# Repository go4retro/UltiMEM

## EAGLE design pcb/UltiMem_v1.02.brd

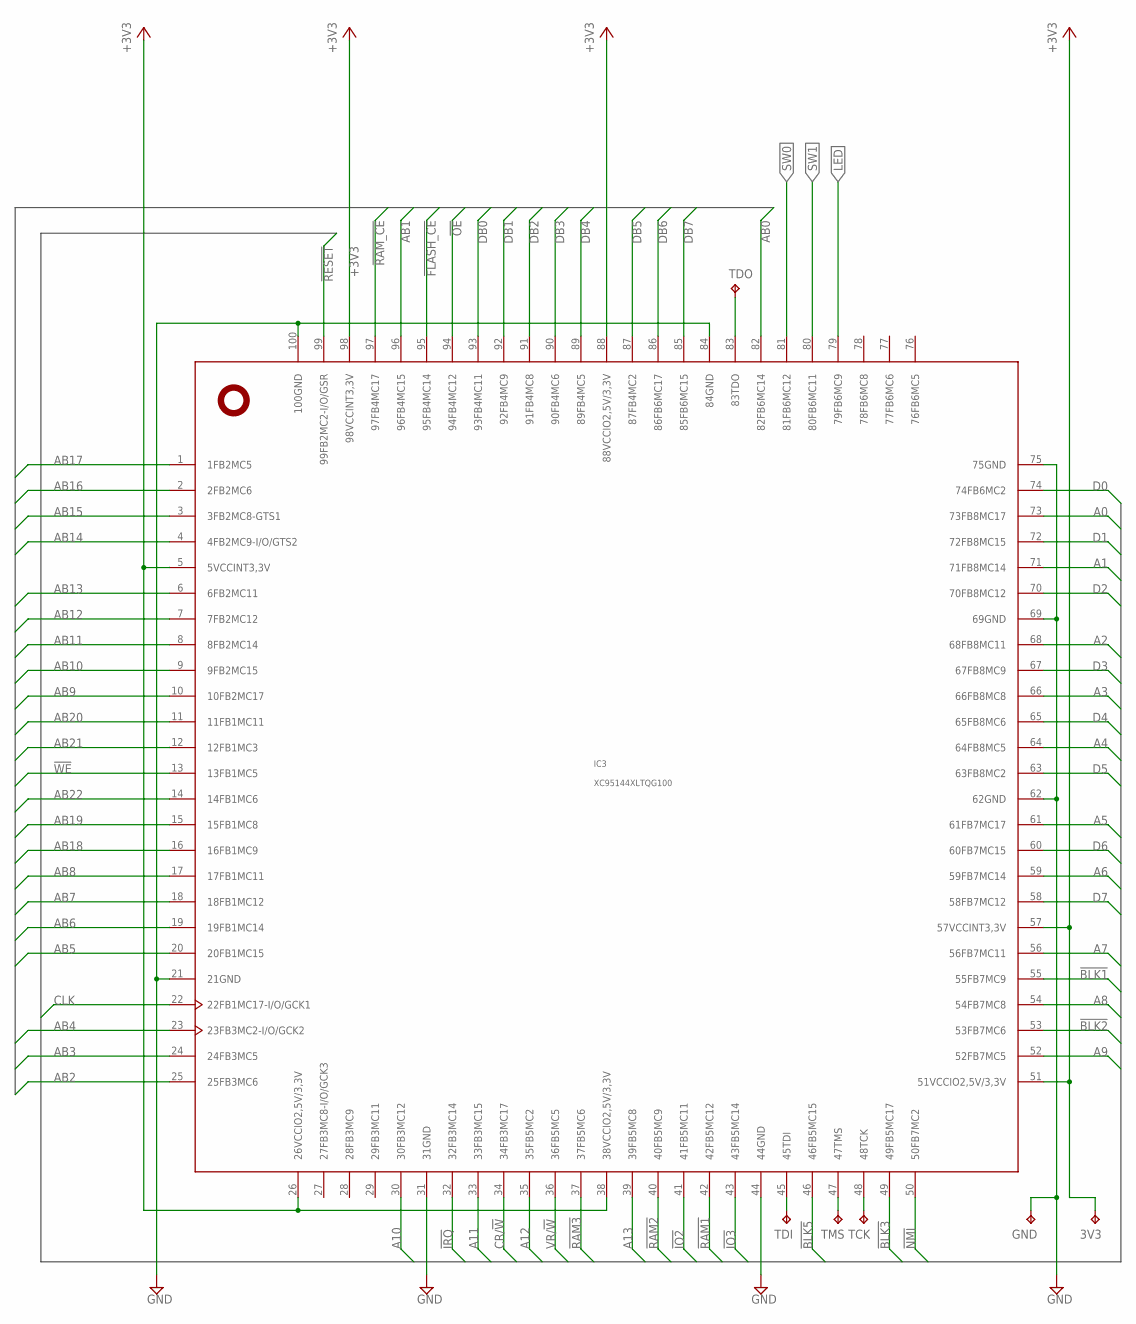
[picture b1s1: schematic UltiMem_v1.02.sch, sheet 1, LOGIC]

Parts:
3V3: TPTP08R; TP08R
GND: TPTP08R; TP08R
IC3: XC95144XLTQG100; TQFP100
TCK: TPTP08R; TP08R
TDI: TPTP08R; TP08R
TDO: TPTP08R; TP08R
TMS: TPTP08R; TP08R

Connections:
!BLK1: IC3.55 (55FB7MC9); also elsewhere on the board
!BLK2: IC3.53 (53FB7MC6); also elsewhere on the board
!BLK3: IC3.49 (49FB5MC17); also elsewhere on the board
!BLK5: IC3.46 (46FB5MC15); also elsewhere on the board
!FLASH_CE: IC3.95 (95FB4MC14); also elsewhere on the board
!IO2: IC3.41 (41FB5MC11); also elsewhere on the board
!IO3: IC3.43 (43FB5MC14); also elsewhere on the board
!IRQ: IC3.32 (32FB3MC14); also elsewhere on the board
!NMI: IC3.50 (50FB7MC2); also elsewhere on the board
!OE: IC3.94 (94FB4MC12); also elsewhere on the board
!RAM1: IC3.42 (42FB5MC12); also elsewhere on the board
!RAM2: IC3.40 (40FB5MC9); also elsewhere on the board
!RAM3: IC3.37 (37FB5MC6); also elsewhere on the board
!RAM_CE: IC3.97 (97FB4MC17); also elsewhere on the board
!RESET: IC3.99 (99FB2MC2-I/O/GSR); also elsewhere on the board
!WE: IC3.13 (13FB1MC5); also elsewhere on the board
+3V3: 3V3.TP, IC3.5 (5VCCINT3,3V), IC3.26 (26VCCIO2,5V/3,3V), IC3.38 (38VCCIO2,5V/3,3V), IC3.51 (51VCCIO2,5V/3,3V), IC3.57 (57VCCINT3,3V), IC3.88 (88VCCIO2,5V/3,3V), IC3.98 (98VCCINT3,3V); also elsewhere on the board
A0: IC3.73 (73FB8MC17); also elsewhere on the board
A1: IC3.71 (71FB8MC14); also elsewhere on the board
A2: IC3.68 (68FB8MC11); also elsewhere on the board
A3: IC3.66 (66FB8MC8); also elsewhere on the board
A4: IC3.64 (64FB8MC5); also elsewhere on the board
A5: IC3.61 (61FB7MC17); also elsewhere on the board
A6: IC3.59 (59FB7MC14); also elsewhere on the board
A7: IC3.56 (56FB7MC11); also elsewhere on the board
A8: IC3.54 (54FB7MC8); also elsewhere on the board
A9: IC3.52 (52FB7MC5); also elsewhere on the board
A10: IC3.30 (30FB3MC12); also elsewhere on the board
A11: IC3.33 (33FB3MC15); also elsewhere on the board
A12: IC3.35 (35FB5MC2); also elsewhere on the board
A13: IC3.39 (39FB5MC8); also elsewhere on the board
AB0: IC3.82 (82FB6MC14); also elsewhere on the board
AB1: IC3.96 (96FB4MC15); also elsewhere on the board
AB2: IC3.25 (25FB3MC6); also elsewhere on the board
AB3: IC3.24 (24FB3MC5); also elsewhere on the board
AB4: IC3.23 (23FB3MC2-I/O/GCK2); also elsewhere on the board
AB5: IC3.20 (20FB1MC15); also elsewhere on the board
AB6: IC3.19 (19FB1MC14); also elsewhere on the board
AB7: IC3.18 (18FB1MC12); also elsewhere on the board
AB8: IC3.17 (17FB1MC11); also elsewhere on the board
AB9: IC3.10 (10FB2MC17); also elsewhere on the board
AB10: IC3.9 (9FB2MC15); also elsewhere on the board
AB11: IC3.8 (8FB2MC14); also elsewhere on the board
AB12: IC3.7 (7FB2MC12); also elsewhere on the board
AB13: IC3.6 (6FB2MC11); also elsewhere on the board
AB14: IC3.4 (4FB2MC9-I/O/GTS2); also elsewhere on the board
AB15: IC3.3 (3FB2MC8-GTS1); also elsewhere on the board
AB16: IC3.2 (2FB2MC6); also elsewhere on the board
AB17: IC3.1 (1FB2MC5); also elsewhere on the board
AB18: IC3.16 (16FB1MC9); also elsewhere on the board
AB19: IC3.15 (15FB1MC8); also elsewhere on the board
AB20: IC3.11 (11FB1MC11); also elsewhere on the board
AB21: IC3.12 (12FB1MC3); also elsewhere on the board
AB22: IC3.14 (14FB1MC6); also elsewhere on the board
CLK: IC3.22 (22FB1MC17-I/O/GCK1); also elsewhere on the board
CR/!W: IC3.34 (34FB3MC17); also elsewhere on the board
D0: IC3.74 (74FB6MC2); also elsewhere on the board
D1: IC3.72 (72FB8MC15); also elsewhere on the board
D2: IC3.70 (70FB8MC12); also elsewhere on the board
D3: IC3.67 (67FB8MC9); also elsewhere on the board
D4: IC3.65 (65FB8MC6); also elsewhere on the board
D5: IC3.63 (63FB8MC2); also elsewhere on the board
D6: IC3.60 (60FB7MC15); also elsewhere on the board
D7: IC3.58 (58FB7MC12); also elsewhere on the board
DB0: IC3.93 (93FB4MC11); also elsewhere on the board
DB1: IC3.92 (92FB4MC9); also elsewhere on the board
DB2: IC3.91 (91FB4MC8); also elsewhere on the board
DB3: IC3.90 (90FB4MC6); also elsewhere on the board
DB4: IC3.89 (89FB4MC5); also elsewhere on the board
DB5: IC3.87 (87FB4MC2); also elsewhere on the board
DB6: IC3.86 (86FB6MC17); also elsewhere on the board
DB7: IC3.85 (85FB6MC15); also elsewhere on the board
GND: GND.TP, IC3.21 (21GND), IC3.31 (31GND), IC3.44 (44GND), IC3.62 (62GND), IC3.69 (69GND), IC3.75 (75GND), IC3.84 (84GND), IC3.100 (100GND); also elsewhere on the board
LED: IC3.79 (79FB6MC9); also elsewhere on the board
unnamed: IC3.45 (45TDI), TDI.TP
unnamed: IC3.47 (47TMS), TMS.TP
unnamed: IC3.48 (48TCK), TCK.TP
unnamed: IC3.83 (83TDO), TDO.TP
SW0: IC3.81 (81FB6MC12); also elsewhere on the board
SW1: IC3.80 (80FB6MC11); also elsewhere on the board
VR/!W: IC3.36 (36FB5MC5); also elsewhere on the board

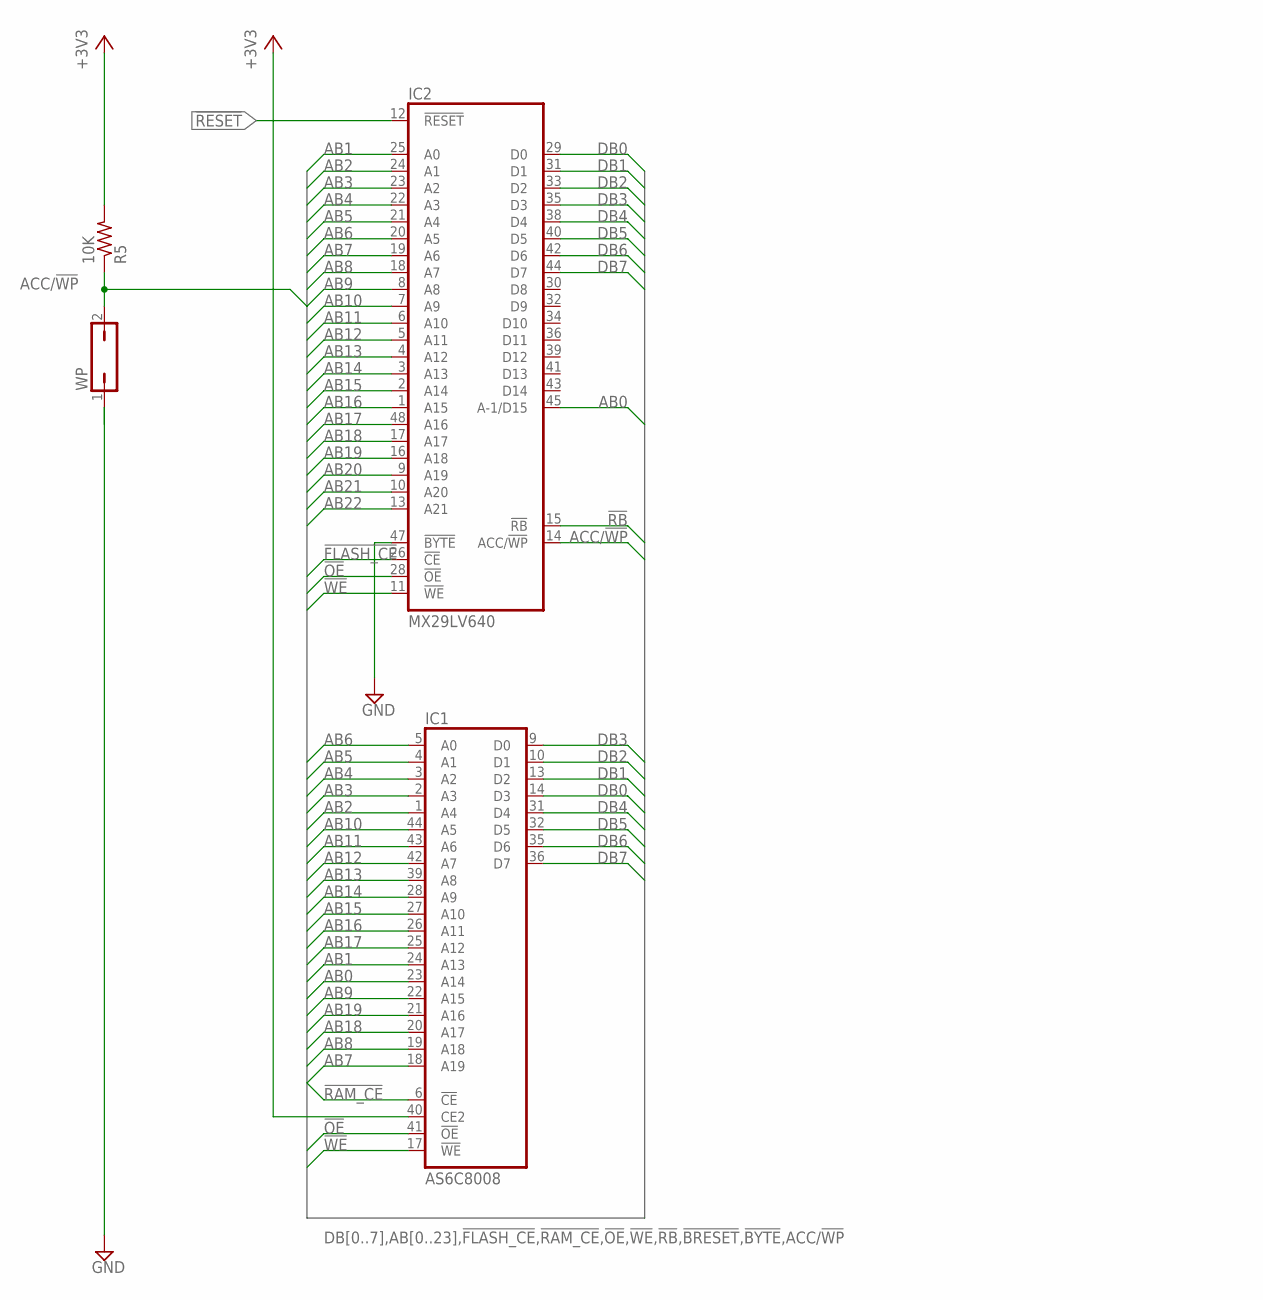
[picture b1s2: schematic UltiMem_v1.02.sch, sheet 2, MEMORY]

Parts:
IC1: AS6C8008; TSOP44
IC2: MX29LV640; TSOP48
R5: 10K; R0402
WP: JP1Q; JP1

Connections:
!FLASH_CE: IC2.26 (!CE); also elsewhere on the board
!OE: IC1.41 (!OE), IC2.28 (!OE); also elsewhere on the board
!RAM_CE: IC1.6 (!CE); also elsewhere on the board
!RB: IC2.15 (!RB)
!RESET: IC2.12 (!RESET); also elsewhere on the board
!WE: IC1.17 (!WE), IC2.11 (!WE); also elsewhere on the board
+3V3: IC1.40 (CE2), R5.2; also elsewhere on the board
AB0: IC1.23 (A14), IC2.45 (A-1/D15); also elsewhere on the board
AB1: IC1.24 (A13), IC2.25 (A0); also elsewhere on the board
AB2: IC1.1 (A4), IC2.24 (A1); also elsewhere on the board
AB3: IC1.2 (A3), IC2.23 (A2); also elsewhere on the board
AB4: IC1.3 (A2), IC2.22 (A3); also elsewhere on the board
AB5: IC1.4 (A1), IC2.21 (A4); also elsewhere on the board
AB6: IC1.5 (A0), IC2.20 (A5); also elsewhere on the board
AB7: IC1.18 (A19), IC2.19 (A6); also elsewhere on the board
AB8: IC1.19 (A18), IC2.18 (A7); also elsewhere on the board
AB9: IC1.22 (A15), IC2.8 (A8); also elsewhere on the board
AB10: IC1.44 (A5), IC2.7 (A9); also elsewhere on the board
AB11: IC1.43 (A6), IC2.6 (A10); also elsewhere on the board
AB12: IC1.42 (A7), IC2.5 (A11); also elsewhere on the board
AB13: IC1.39 (A8), IC2.4 (A12); also elsewhere on the board
AB14: IC1.28 (A9), IC2.3 (A13); also elsewhere on the board
AB15: IC1.27 (A10), IC2.2 (A14); also elsewhere on the board
AB16: IC1.26 (A11), IC2.1 (A15); also elsewhere on the board
AB17: IC1.25 (A12), IC2.48 (A16); also elsewhere on the board
AB18: IC1.20 (A17), IC2.17 (A17); also elsewhere on the board
AB19: IC1.21 (A16), IC2.16 (A18); also elsewhere on the board
AB20: IC2.9 (A19); also elsewhere on the board
AB21: IC2.10 (A20); also elsewhere on the board
AB22: IC2.13 (A21); also elsewhere on the board
ACC/!WP: IC2.14 (ACC/!WP), R5.1, WP.2
DB0: IC1.14 (D3), IC2.29 (D0); also elsewhere on the board
DB1: IC1.13 (D2), IC2.31 (D1); also elsewhere on the board
DB2: IC1.10 (D1), IC2.33 (D2); also elsewhere on the board
DB3: IC1.9 (D0), IC2.35 (D3); also elsewhere on the board
DB4: IC1.31 (D4), IC2.38 (D4); also elsewhere on the board
DB5: IC1.32 (D5), IC2.40 (D5); also elsewhere on the board
DB6: IC1.35 (D6), IC2.42 (D6); also elsewhere on the board
DB7: IC1.36 (D7), IC2.44 (D7); also elsewhere on the board
GND: IC2.47 (!BYTE), WP.1; also elsewhere on the board

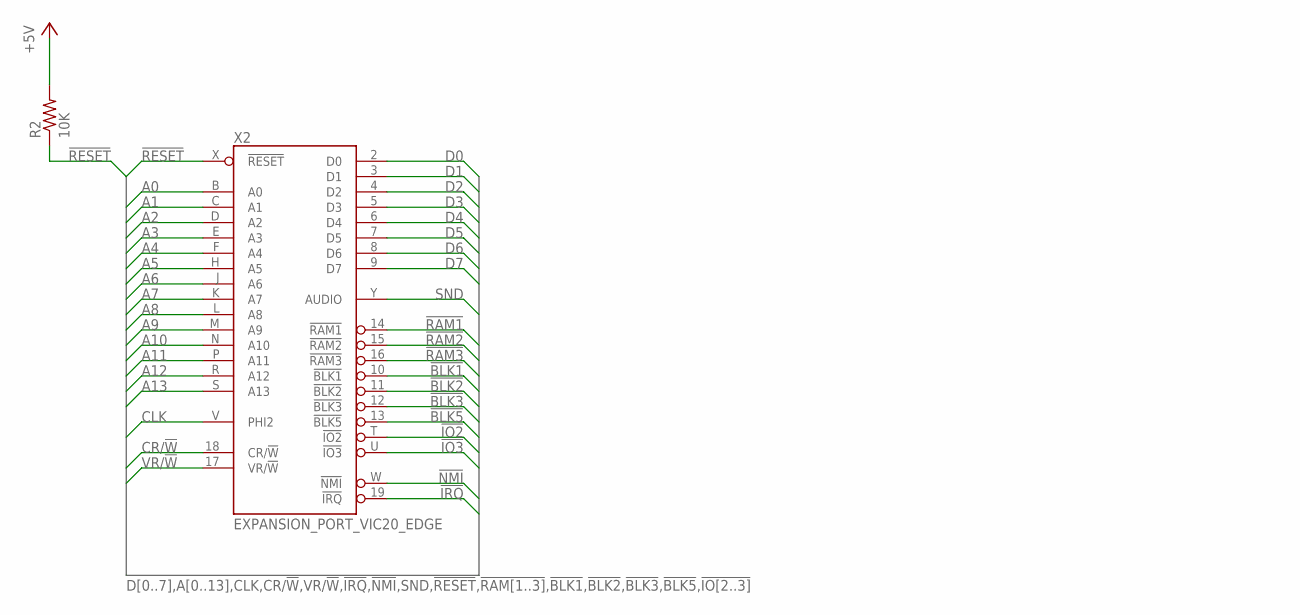
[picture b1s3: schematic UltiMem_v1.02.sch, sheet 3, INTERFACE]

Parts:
R2: 10K; R0402
X2: EXPANSION_PORT_VIC20_EDGE; MA156-22-2

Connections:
!BLK1: X2.10 (!BLK1); also elsewhere on the board
!BLK2: X2.11 (!BLK2); also elsewhere on the board
!BLK3: X2.12 (!BLK3); also elsewhere on the board
!BLK5: X2.13 (!BLK5); also elsewhere on the board
!IO2: X2.T (!IO2); also elsewhere on the board
!IO3: X2.U (!IO3); also elsewhere on the board
!IRQ: X2.19 (!IRQ); also elsewhere on the board
!NMI: X2.W (!NMI); also elsewhere on the board
!RAM1: X2.14 (!RAM1); also elsewhere on the board
!RAM2: X2.15 (!RAM2); also elsewhere on the board
!RAM3: X2.16 (!RAM3); also elsewhere on the board
!RESET: R2.1, X2.X (!RESET); also elsewhere on the board
+5V: R2.2; also elsewhere on the board
A0: X2.B (A0); also elsewhere on the board
A1: X2.C (A1); also elsewhere on the board
A2: X2.D (A2); also elsewhere on the board
A3: X2.E (A3); also elsewhere on the board
A4: X2.F (A4); also elsewhere on the board
A5: X2.H (A5); also elsewhere on the board
A6: X2.J (A6); also elsewhere on the board
A7: X2.K (A7); also elsewhere on the board
A8: X2.L (A8); also elsewhere on the board
A9: X2.M (A9); also elsewhere on the board
A10: X2.N (A10); also elsewhere on the board
A11: X2.P (A11); also elsewhere on the board
A12: X2.R (A12); also elsewhere on the board
A13: X2.S (A13); also elsewhere on the board
CLK: X2.V (PHI2); also elsewhere on the board
CR/!W: X2.18 (CR/!W); also elsewhere on the board
D0: X2.2 (D0); also elsewhere on the board
D1: X2.3 (D1); also elsewhere on the board
D2: X2.4 (D2); also elsewhere on the board
D3: X2.5 (D3); also elsewhere on the board
D4: X2.6 (D4); also elsewhere on the board
D5: X2.7 (D5); also elsewhere on the board
D6: X2.8 (D6); also elsewhere on the board
D7: X2.9 (D7); also elsewhere on the board
SND: X2.Y (AUDIO)
VR/!W: X2.17 (VR/!W); also elsewhere on the board

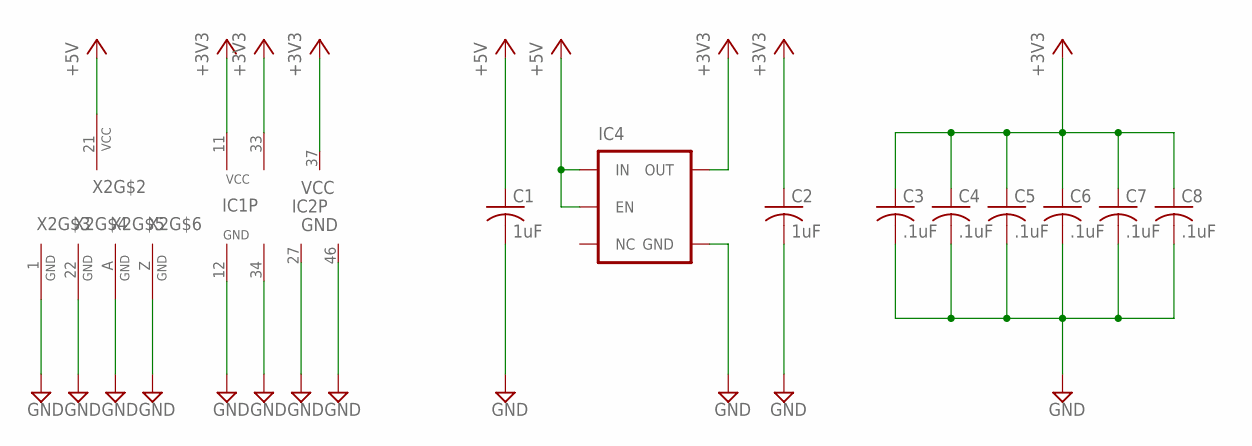
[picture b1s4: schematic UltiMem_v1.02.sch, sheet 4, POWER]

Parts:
C1, C2: 1uF; C0402
C3, C4, C5, C6, C7, C8: .1uF; C0402
IC1: AS6C8008; TSOP44
IC2: MX29LV640; TSOP48
IC4: V_REG_TPS76433SOT23-5; SOT23-5
X2: EXPANSION_PORT_VIC20_EDGE; MA156-22-2

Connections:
+3V3: C2.1, C3.1, C4.1, C5.1, C6.1, C7.1, C8.1, IC1.11 (VCC), IC1.33 (VCC), IC2.37 (VCC), IC4.5 (OUT); also elsewhere on the board
+5V: C1.1, IC4.1 (IN), IC4.3 (EN), X2.21 (VCC); also elsewhere on the board
GND: C1.2, C2.2, C3.2, C4.2, C5.2, C6.2, C7.2, C8.2, IC1.12 (GND), IC1.34 (GND), IC2.27 (GND), IC2.46 (GND), IC4.2 (GND), X2.1 (GND), X2.22 (GND), X2.A (GND), X2.Z (GND); also elsewhere on the board

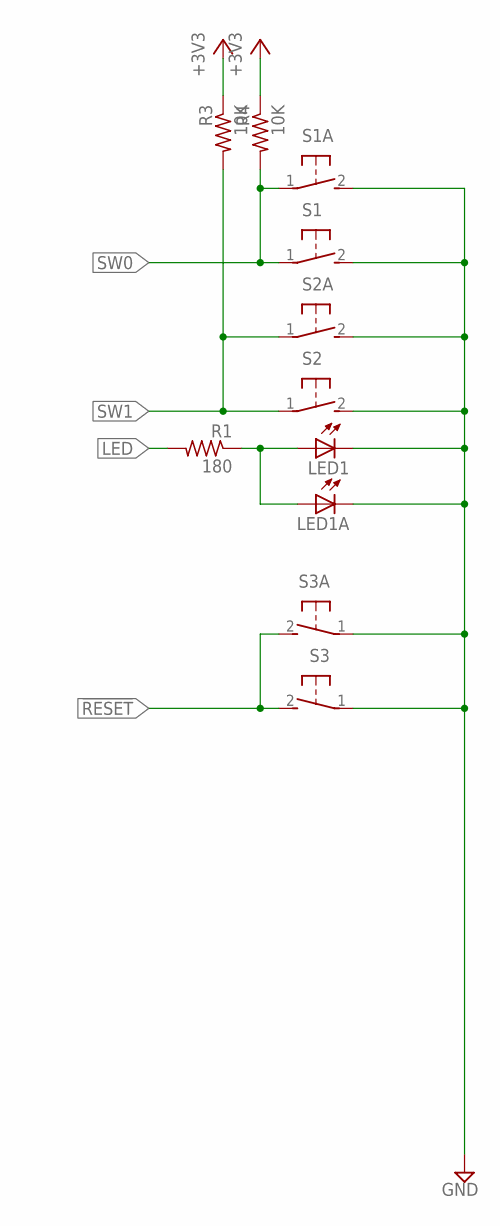
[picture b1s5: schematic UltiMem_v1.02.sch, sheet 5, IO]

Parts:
LED1, LED1A: LED3MM
R1: 180; R0402
R3, R4: 10K; R0402
S1, S1A, S2, S2A, S3, S3A: 31-XX; B3F-31XX

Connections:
!RESET: S3.2 (S), S3A.2 (S); also elsewhere on the board
+3V3: R3.1, R4.1; also elsewhere on the board
GND: LED1.K (C), LED1A.K (C), S1.2 (S), S1A.2 (S), S2.2 (S), S2A.2 (S), S3.1, S3A.1; also elsewhere on the board
LED: R1.2; also elsewhere on the board
unnamed: LED1.A, LED1A.A, R1.1
SW0: R4.2, S1.1, S1A.1; also elsewhere on the board
SW1: R3.2, S2.1, S2A.1; also elsewhere on the board

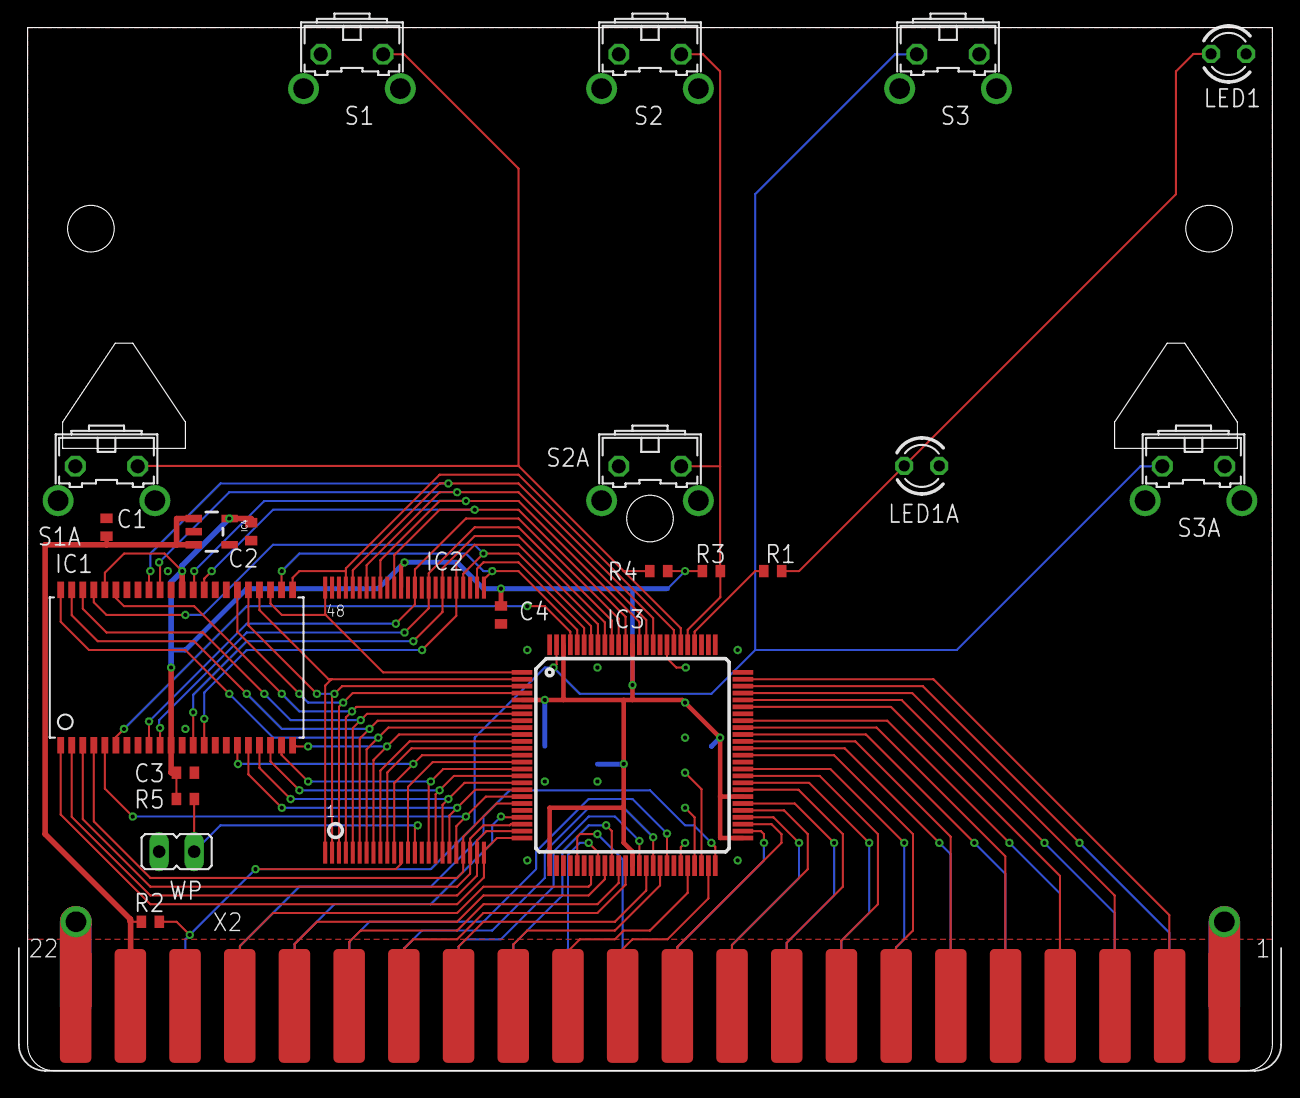
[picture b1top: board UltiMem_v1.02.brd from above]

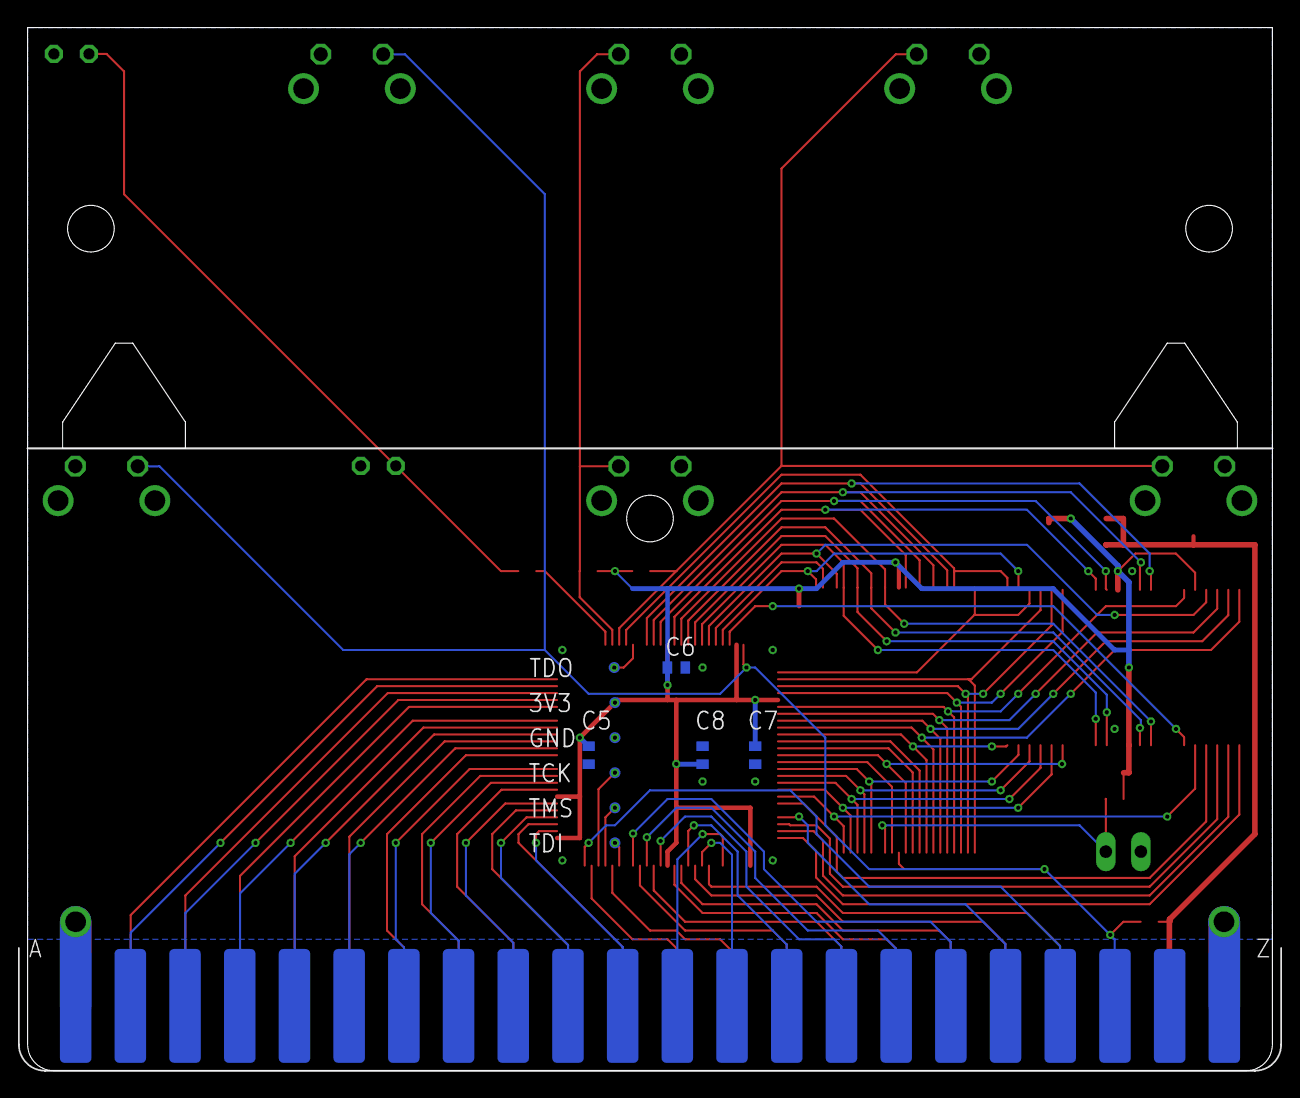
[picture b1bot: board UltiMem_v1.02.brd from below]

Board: 2 copper layers, 90.2 x 75.6 mm, 33 parts (10 on the bottom side), 84 nets.

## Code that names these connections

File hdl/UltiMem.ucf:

#PACE: Start of Constraints generated by PACE

#PACE: Start of PACE I/O Pin Assignments
NET "address<0>"  LOC = "P73"  ; 
NET "address<10>"  LOC = "P30"  ; 
NET "address<11>"  LOC = "P33"  ; 
NET "address<12>"  LOC = "P35"  ; 
NET "address<1>"  LOC = "P71"  ; 
NET "address<2>"  LOC = "P68"  ; 
NET "address<3>"  LOC = "P66"  ; 
NET "address<4>"  LOC = "P64"  ; 
NET "address<5>"  LOC = "P61"  ; 
NET "address<6>"  LOC = "P59"  ; 
NET "address<7>"  LOC = "P56"  ; 
NET "address<8>"  LOC = "P54"  ; 
NET "address<9>"  LOC = "P52"  ; 
NET "baddress<0>"  LOC = "P82"  ; 
NET "baddress<10>"  LOC = "P9"  ; 
NET "baddress<11>"  LOC = "P8"  ; 
NET "baddress<12>"  LOC = "P7"  ; 
NET "baddress<13>"  LOC = "P6"  ; 
NET "baddress<14>"  LOC = "P4"  ; 
NET "baddress<15>"  LOC = "P3"  ; 
NET "baddress<16>"  LOC = "P2"  ; 
NET "baddress<17>"  LOC = "P1"  ; 
NET "baddress<18>"  LOC = "P16"  ; 
NET "baddress<19>"  LOC = "P15"  ; 
NET "baddress<1>"  LOC = "P96"  ; 
NET "baddress<20>"  LOC = "P11"  ; 
NET "baddress<21>"  LOC = "P12"  ; 
NET "baddress<22>"  LOC = "P14"  ; 
NET "baddress<2>"  LOC = "P25"  ; 
NET "baddress<3>"  LOC = "P24"  ; 
NET "baddress<4>"  LOC = "P23"  ; 
NET "baddress<5>"  LOC = "P20"  ; 
NET "baddress<6>"  LOC = "P19"  ; 
NET "baddress<7>"  LOC = "P18"  ; 
NET "baddress<8>"  LOC = "P17"  ; 
NET "baddress<9>"  LOC = "P10"  ; 
NET "bdata<0>"  LOC = "P93"  ; 
NET "bdata<1>"  LOC = "P92"  ; 
NET "bdata<2>"  LOC = "P91"  ; 
NET "bdata<3>"  LOC = "P90"  ; 
NET "bdata<4>"  LOC = "P89"  ; 
NET "bdata<5>"  LOC = "P87"  ; 
NET "bdata<6>"  LOC = "P86"  ; 
NET "bdata<7>"  LOC = "P85"  ; 
NET "blk1"  LOC = "P55"  ; 
NET "blk2"  LOC = "P53"  ; 
NET "blk3"  LOC = "P49"  ; 
NET "blk5"  LOC = "P46"  ; 
NET "clock"  LOC = "P22"  ; 
NET "data<0>"  LOC = "P74"  ; 
NET "data<1>"  LOC = "P72"  ; 
NET "data<2>"  LOC = "P70"  ; 
NET "data<3>"  LOC = "P67"  ; 
NET "data<4>"  LOC = "P65"  ; 
NET "data<5>"  LOC = "P63"  ; 
NET "data<6>"  LOC = "P60"  ; 
NET "data<7>"  LOC = "P58"  ; 
NET "flash_ce"  LOC = "P95"  ; 
NET "io<2>"  LOC = "P41"  ; 
NET "io<3>"  LOC = "P43"  ; 
NET "irq"  LOC = "P32"  ; 
NET "led"  LOC = "P79"  ; 
NET "nmi"  LOC = "P50"  ; 
NET "oe"  LOC = "P94"  ; 
NET "r_w"  LOC = "P34"  ; 
NET "ram1"  LOC = "P42"  ; 
NET "ram2"  LOC = "P40"  ; 
NET "ram3"  LOC = "P37"  ; 
NET "ram_ce"  LOC = "P97"  ; 
NET "reset"  LOC = "P99"  ; 
NET "switch<0>"  LOC = "P80"  ; 
NET "switch<1>"  LOC = "P81"  ; 
NET "we"  LOC = "P13"  ; 

#PACE: Start of PACE Area Constraints

#PACE: Start of PACE Prohibit Constraints

#PACE: End of Constraints generated by PACE

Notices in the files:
parts and their libraries:
SparkFun: Licensing: CC v3.0 Share-Alike You are welcome to use this library for commercial purposes.
